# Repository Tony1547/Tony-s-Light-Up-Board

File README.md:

# Tony-s-Light-Up-Board
Small board i can take to FRC comps

/ BOM : https://docs.google.com/spreadsheets/d/1fGATLPJ2M_kJRIZs2cyqMHB42CdELpvUBpSz-iXdPng/edit?usp=sharing

(CSV in files as well)

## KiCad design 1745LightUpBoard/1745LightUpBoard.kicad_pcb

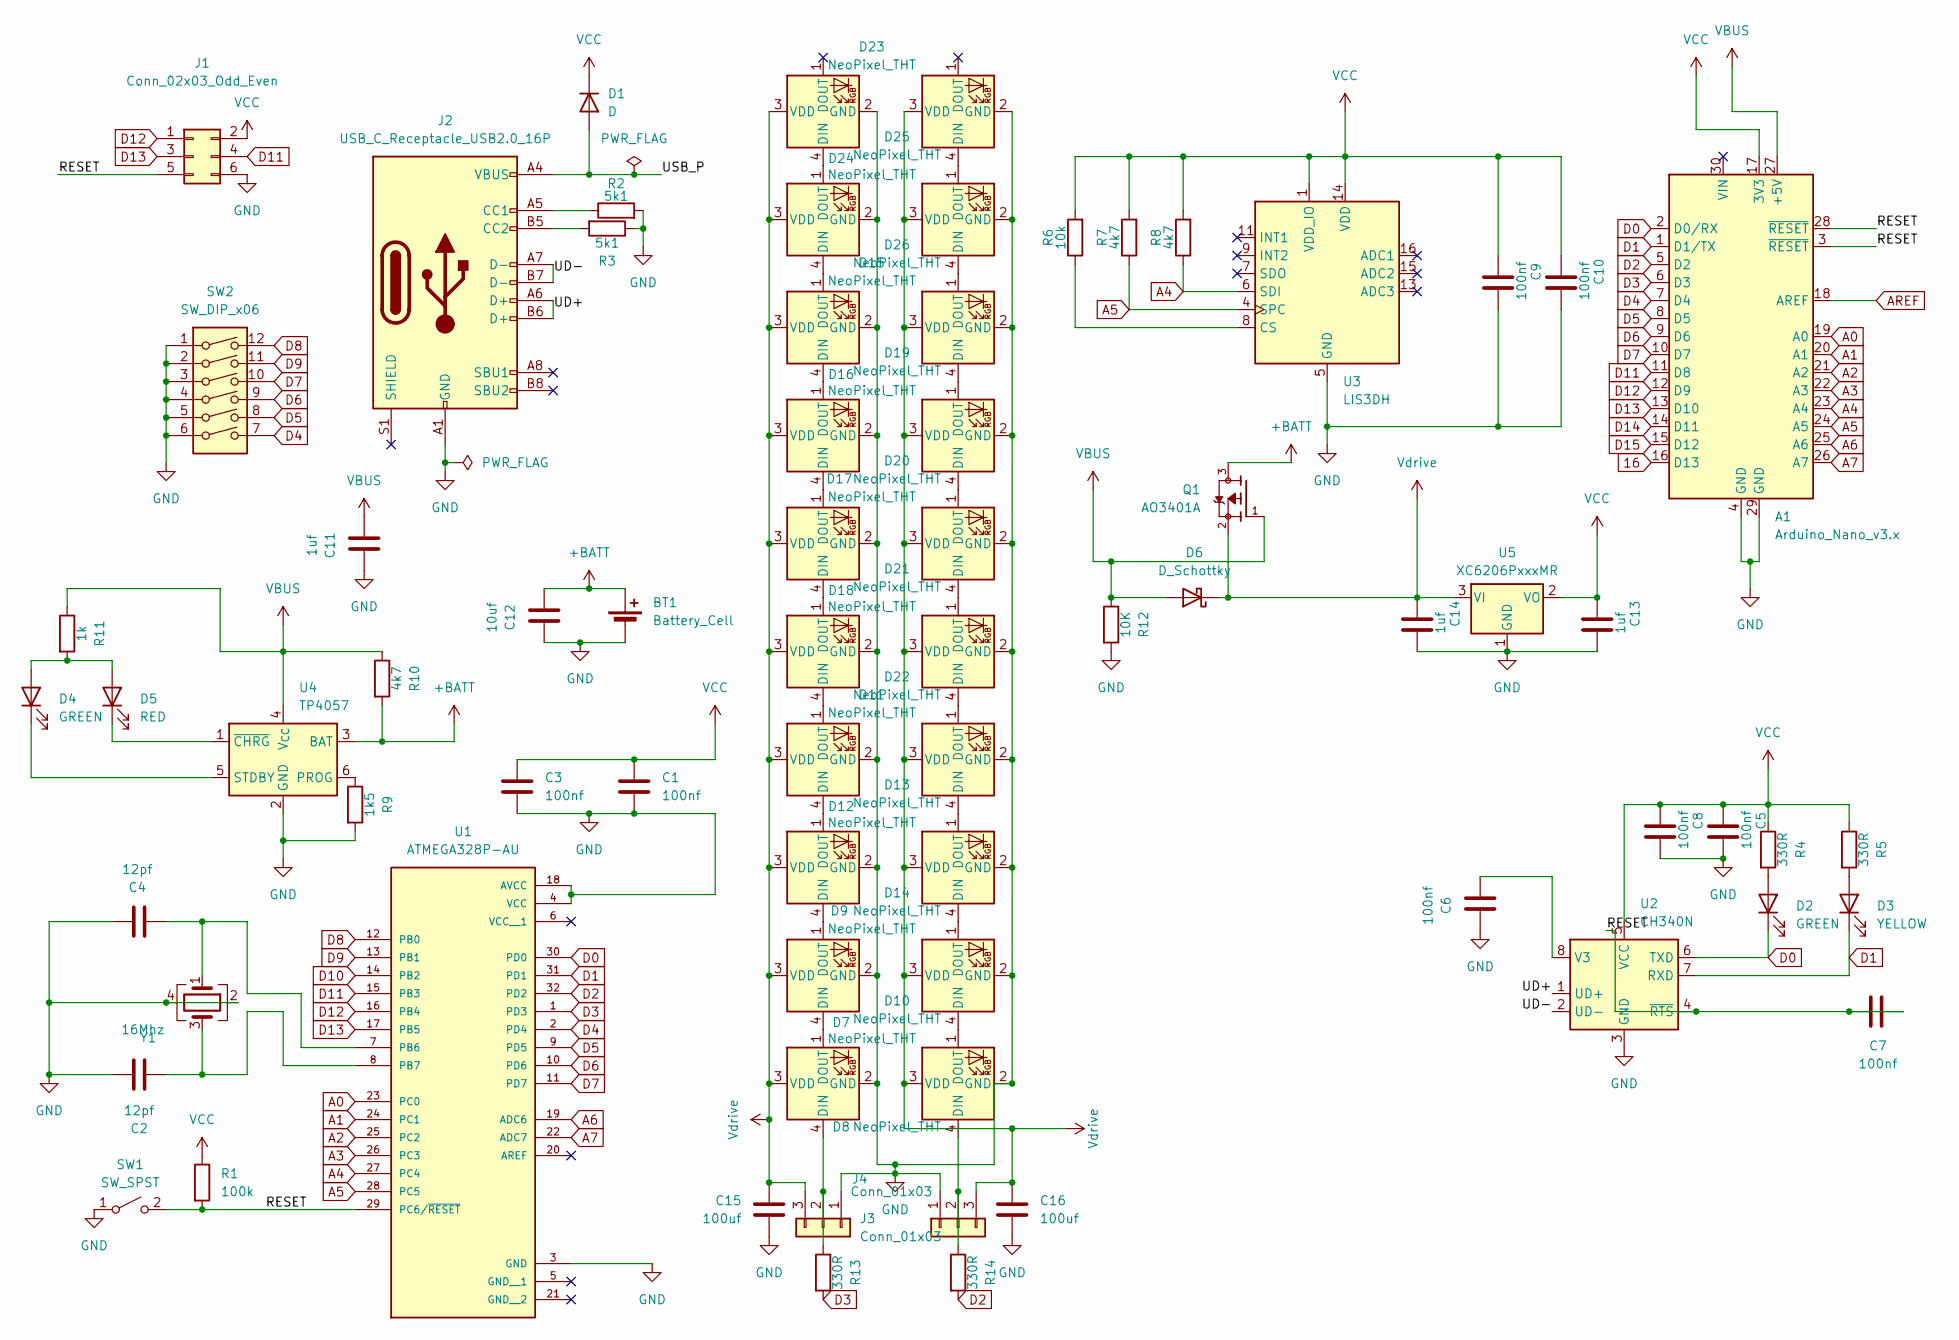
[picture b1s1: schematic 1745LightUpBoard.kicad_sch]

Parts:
A1: Arduino_Nano_v3.x; Arduino_Nano
BT1: Battery_Cell
C1, C3, C5, C6, C7, C8, C9, C10: 100nf; C_0201_0603Metric_Pad0.64x0.40mm_HandSolder
C2, C4: 12pf; C_0201_0603Metric_Pad0.64x0.40mm_HandSolder
C11, C13, C14: 1uf; C_0201_0603Metric_Pad0.64x0.40mm_HandSolder
C12: 10uf; C_0201_0603Metric_Pad0.64x0.40mm_HandSolder
C15, C16: 100uf; C_0201_0603Metric_Pad0.64x0.40mm_HandSolder
D1: D; D_0201_0603Metric_Pad0.64x0.40mm_HandSolder
D2, D4: GREEN; LED_0201_0603Metric_Pad0.64x0.40mm_HandSolder
D3: YELLOW; LED_0201_0603Metric_Pad0.64x0.40mm_HandSolder
D5: RED; LED_0201_0603Metric_Pad0.64x0.40mm_HandSolder
D6: D_Schottky; D_0201_0603Metric_Pad0.64x0.40mm_HandSolder
D7, D8, D9, D10, D11, D12, D13, D14, D15, D16, D17, D18, D19, D20, D21, D22, D23, D24, D25, D26: NeoPixel_THT; LED_D5.0mm-4_RGB
J1: Conn_02x03_Odd_Even; IDC-Header_2x03_P2.54mm_Horizontal
J2: USB_C_Receptacle_USB2.0_16P; USB_C_Receptacle_Palconn_UTC16-G
J3, J4: Conn_01x03; JST_PH_S3B-PH-K_1x03_P2.00mm_Horizontal
Q1: AO3401A; SOT23-3
R1: 100k; R_0201_0603Metric_Pad0.64x0.40mm_HandSolder
R2, R3: 5k1; R_0201_0603Metric_Pad0.64x0.40mm_HandSolder
R4, R5, R13, R14: 330R; R_0201_0603Metric_Pad0.64x0.40mm_HandSolder
R6: 10k; R_0201_0603Metric_Pad0.64x0.40mm_HandSolder
R7, R8, R10: 4k7; R_0201_0603Metric_Pad0.64x0.40mm_HandSolder
R9: 1k5; R_0201_0603Metric_Pad0.64x0.40mm_HandSolder
R11: 1k; R_0201_0603Metric_Pad0.64x0.40mm_HandSolder
R12: 10K; R_0201_0603Metric_Pad0.64x0.40mm_HandSolder
SW1: SW_SPST
SW2: SW_DIP_x06
U1: ATMEGA328P-AU; QFP80P900X900X120-32N; PARTREV 8271A
U2: CH340N; JEITA_SOIC-8_3.9x4.9mm_P1.27mm
U3: LIS3DH; LGA-16_3x3mm_P0.5mm_LayoutBorder3x5y
U4: TP4057; TSOT-23-6
U5: XC6206PxxxMR; SOT-23-3
Y1: 16Mhz; Crystal_SMD_0603-4Pin_6.0x3.5mm_HandSoldering

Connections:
16: A1.16 (D13)
+BATT: BT1.1 (+), C12.1, Q1.3, R10.2, U4.3 (BAT)
/RESET: A1.3 (~RESET), A1.28 (~RESET), C7.1, C7.2, J1.5, R1.2, SW1.2 (B), U1.29 (PC6/~RESET), U2.4 (~RTS)
/UD+: J2.A6 (D+), J2.B6 (D+), U2.1 (UD+)
/UD-: J2.A7 (D-), J2.B7 (D-), U2.2 (UD-)
/USB_P: D1.2 (A), J2.A4 (VBUS), J2.A9 (VBUS), J2.B4 (VBUS), J2.B9 (VBUS)
A0: A1.19 (A0), U1.23 (PC0)
A1: A1.20 (A1), U1.24 (PC1)
A2: A1.21 (A2), U1.25 (PC2)
A3: A1.22 (A3), U1.26 (PC3)
A4: A1.23 (A4), R8.1, U1.27 (PC4), U3.6 (SDI)
A5: A1.24 (A5), R7.1, U1.28 (PC5), U3.4 (SPC)
A6: A1.25 (A6), U1.19 (ADC6)
A7: A1.26 (A7), U1.22 (ADC7)
AREF: A1.18 (AREF)
D0: A1.2 (D0/RX), D2.1 (K), U1.30 (PD0), U2.6 (TXD)
D1: A1.1 (D1/TX), D3.1 (K), U1.31 (PD1), U2.7 (RXD)
D2: A1.5 (D2), R14.2, U1.32 (PD2)
D3: A1.6 (D3), R13.2, U1.1 (PD3)
D4: A1.7 (D4), SW2.7, U1.2 (PD4)
D5: A1.8 (D5), SW2.8, U1.9 (PD5)
D6: A1.9 (D6), SW2.9, U1.10 (PD6)
D7: A1.10 (D7), SW2.10, U1.11 (PD7)
D8: SW2.12, U1.12 (PB0)
D9: SW2.11, U1.13 (PB1)
D10: U1.14 (PB2)
D11: A1.11 (D8), J1.4, U1.15 (PB3)
D12: A1.12 (D9), J1.1, U1.16 (PB4)
D13: A1.13 (D10), J1.3, U1.17 (PB5)
D14: A1.14 (D11)
D15: A1.15 (D12)
GND: A1.4 (GND), A1.29 (GND), BT1.2 (-), C1.2, C2.2, C3.2, C4.2, C5.2, C6.2, C8.2, C9.2, C10.2, C11.2, C12.2, C13.2, C14.2, C15.2, C16.2, D7.2 (GND), D8.2 (GND), D9.2 (GND), D10.2 (GND), D11.2 (GND), D12.2 (GND), D13.2 (GND), D14.2 (GND), D15.2 (GND), D16.2 (GND), D17.2 (GND), D18.2 (GND), D19.2 (GND), D20.2 (GND), D21.2 (GND), D22.2 (GND), D23.2 (GND), D24.2 (GND), D25.2 (GND), D26.2 (GND), J1.6, J2.A1 (GND), J2.A12 (GND), J2.B1 (GND), J2.B12 (GND), J3.1, J4.1, R2.2, R3.1, R9.2, R12.2, SW1.1 (A), SW2.1, SW2.2, SW2.3, SW2.4, SW2.5, SW2.6, U1.3 (GND), U1.4 (VCC), U1.18 (AVCC), U2.3 (GND), U3.5 (GND), U3.10 (GND), U3.12 (GND), U4.2 (GND), U5.1 (GND), Y1.2, Y1.4
unnamed: D2.2 (A), R4.2
unnamed: D3.2 (A), R5.2
unnamed: D4.2 (A), D5.2 (A), R11.2
unnamed: D4.1 (K), U4.5 (STDBY)
unnamed: D5.1 (K), U4.1 (~CHRG)
unnamed: D7.4 (DIN), J3.2, R13.1
unnamed: D7.1 (DOUT), D9.4 (DIN)
unnamed: D8.4 (DIN), J4.2, R14.1
unnamed: D8.1 (DOUT), D10.4 (DIN)
unnamed: D10.1 (DOUT), D14.4 (DIN)
unnamed: D11.4 (DIN), D12.1 (DOUT)
unnamed: D11.1 (DOUT), D18.4 (DIN)
unnamed: D9.1 (DOUT), D12.4 (DIN)
unnamed: D13.4 (DIN), D14.1 (DOUT)
unnamed: D13.1 (DOUT), D22.4 (DIN)
unnamed: D15.4 (DIN), D16.1 (DOUT)
unnamed: D15.1 (DOUT), D24.4 (DIN)
unnamed: D16.4 (DIN), D17.1 (DOUT)
unnamed: D17.4 (DIN), D18.1 (DOUT)
unnamed: D19.4 (DIN), D20.1 (DOUT)
unnamed: D19.1 (DOUT), D26.4 (DIN)
unnamed: D20.4 (DIN), D21.1 (DOUT)
unnamed: D21.4 (DIN), D22.1 (DOUT)
unnamed: D23.4 (DIN), D24.1 (DOUT)
unnamed: D25.4 (DIN), D26.1 (DOUT)
unnamed: J2.A5 (CC1), R2.1
unnamed: J2.B5 (CC2), R3.2
unnamed: C4.1, U1.7 (PB6), Y1.1
unnamed: C2.1, U1.8 (PB7), Y1.3
unnamed: C6.1, U2.8 (V3)
unnamed: R6.1, U3.8 (CS)
unnamed: R9.1, U4.6 (PROG)
VBUS: A1.27 (+5V), C11.1, D6.2 (A), Q1.1, R10.1, R11.1, R12.1, U4.4 (V_{CC})
VCC: A1.17 (3V3), C1.1, C3.1, C5.1, C8.1, C9.1, C10.1, C13.1, D1.1 (K), J1.2, R1.1, R4.1, R5.1, R6.2, R7.2, R8.2, U2.5 (VCC), U3.1 (VDD_IO), U3.14 (VDD), U5.2 (VO)
Vdrive: C14.1, C15.1, C16.1, D6.1 (K), D7.3 (VDD), D8.3 (VDD), D9.3 (VDD), D10.3 (VDD), D11.3 (VDD), D12.3 (VDD), D13.3 (VDD), D14.3 (VDD), D15.3 (VDD), D16.3 (VDD), D17.3 (VDD), D18.3 (VDD), D19.3 (VDD), D20.3 (VDD), D21.3 (VDD), D22.3 (VDD), D23.3 (VDD), D24.3 (VDD), D25.3 (VDD), D26.3 (VDD), J3.3, J4.3, Q1.2, U5.3 (VI)

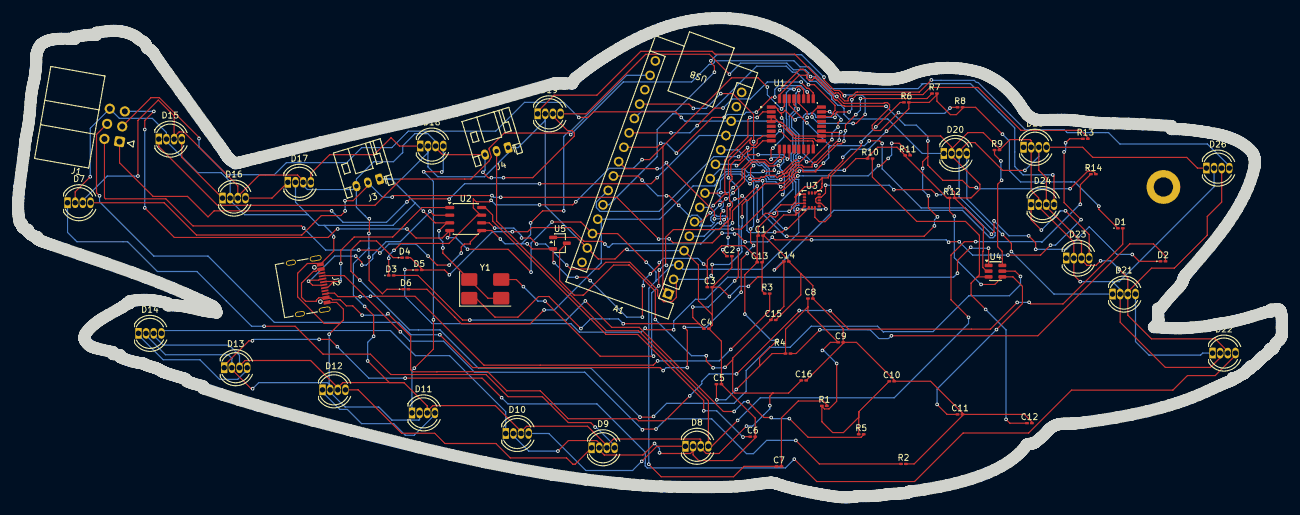
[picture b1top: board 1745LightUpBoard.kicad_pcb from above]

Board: 2 copper layers, 209.6 x 79.5 mm, 67 parts (0 on the bottom side), 60 nets.

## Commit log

2025-11-26 Added PCB Fiiles
